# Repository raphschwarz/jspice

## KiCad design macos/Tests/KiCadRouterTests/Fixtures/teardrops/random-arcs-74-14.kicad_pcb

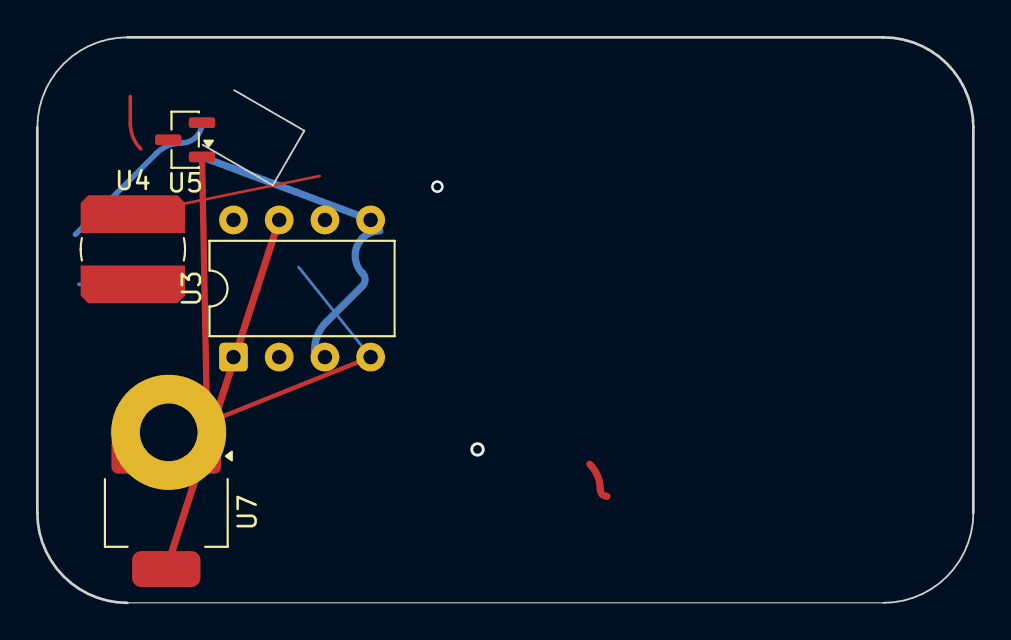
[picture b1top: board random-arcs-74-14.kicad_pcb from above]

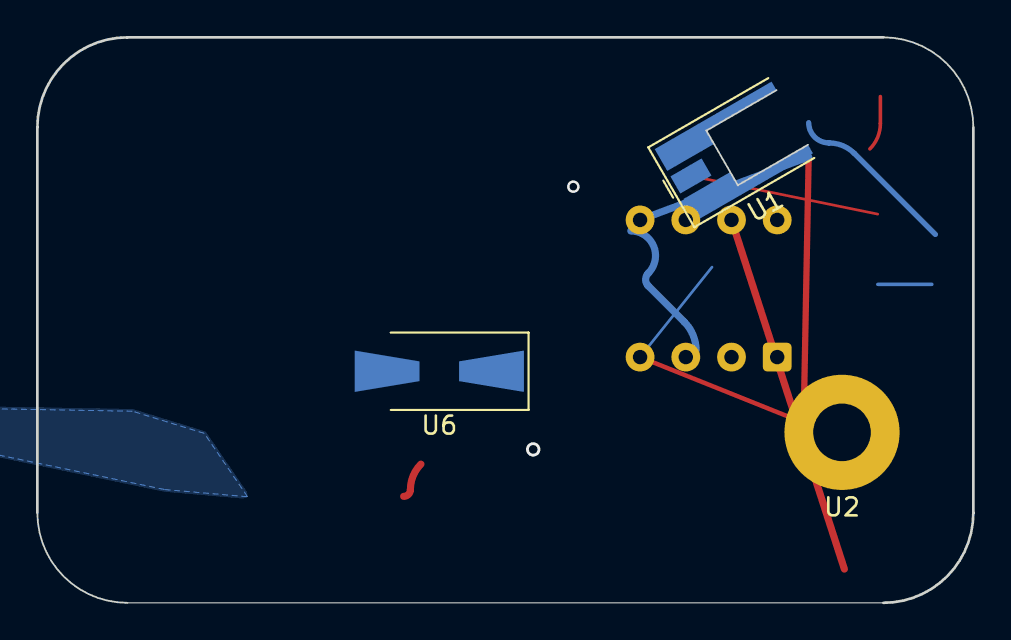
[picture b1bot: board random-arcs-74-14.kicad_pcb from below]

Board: 2 copper layers, 52.0 x 31.4 mm, 7 parts (3 on the bottom side), 6 nets.

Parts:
U1: MMCX_Molex_73415-0961_Horizontal_0.8mm-PCB
U2: MountingHole_3.2mm_M3_Pad
U3: DIP-8_W7.62mm
U4: L_Bourns_SDR0604
U5: SOT-23
U6: D_SMA-SMB_Universal_Handsoldering
U7: SOT-223-3_TabPin2

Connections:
/sub/clk: U3.3, U3.6
D7: U3.2, U6.2, U7.2
N2: U2.1, U3.4
SIG1: U1.1, U5.1, U5.3
SIG2: U6.1, U7.2, U7.3
VCC: U4.2, U5.2

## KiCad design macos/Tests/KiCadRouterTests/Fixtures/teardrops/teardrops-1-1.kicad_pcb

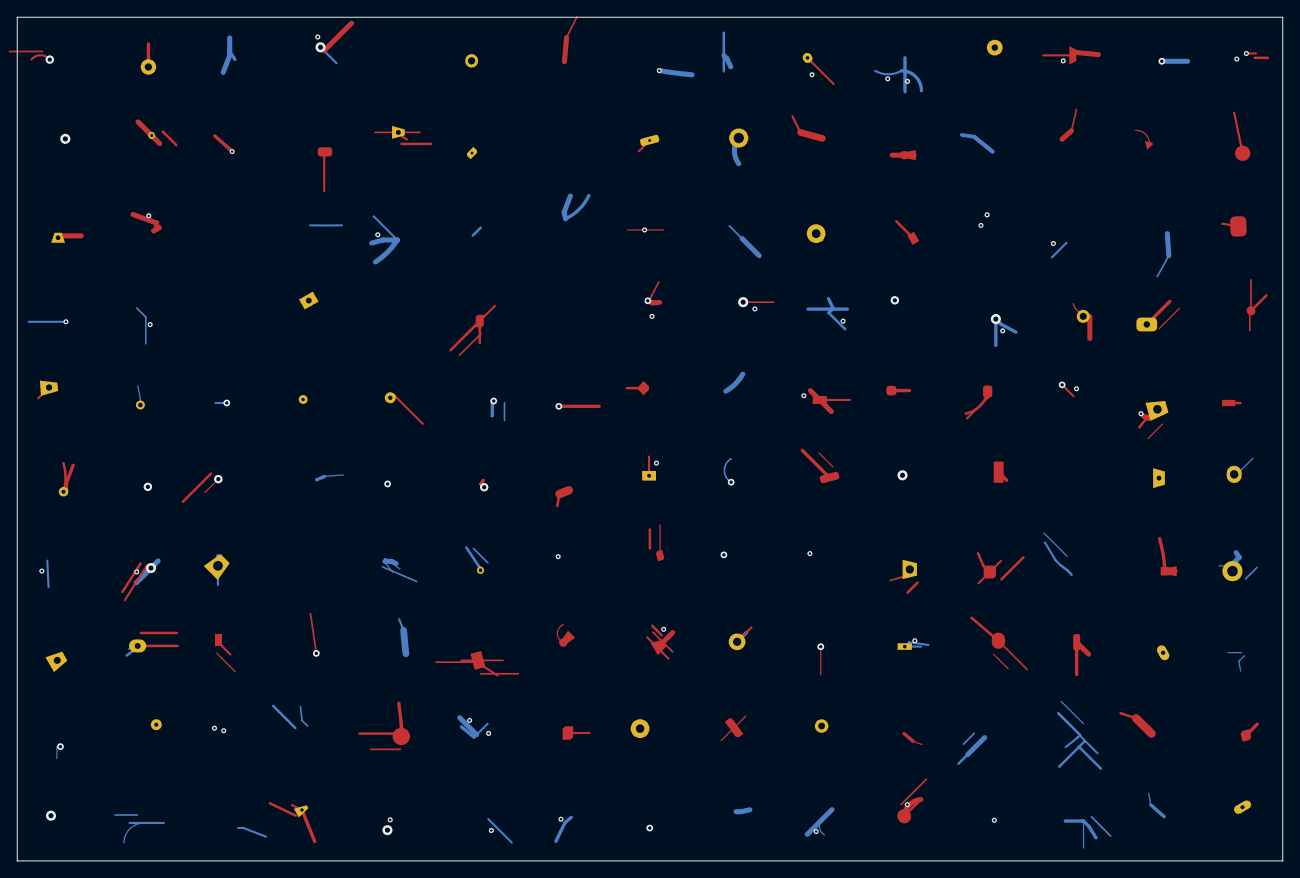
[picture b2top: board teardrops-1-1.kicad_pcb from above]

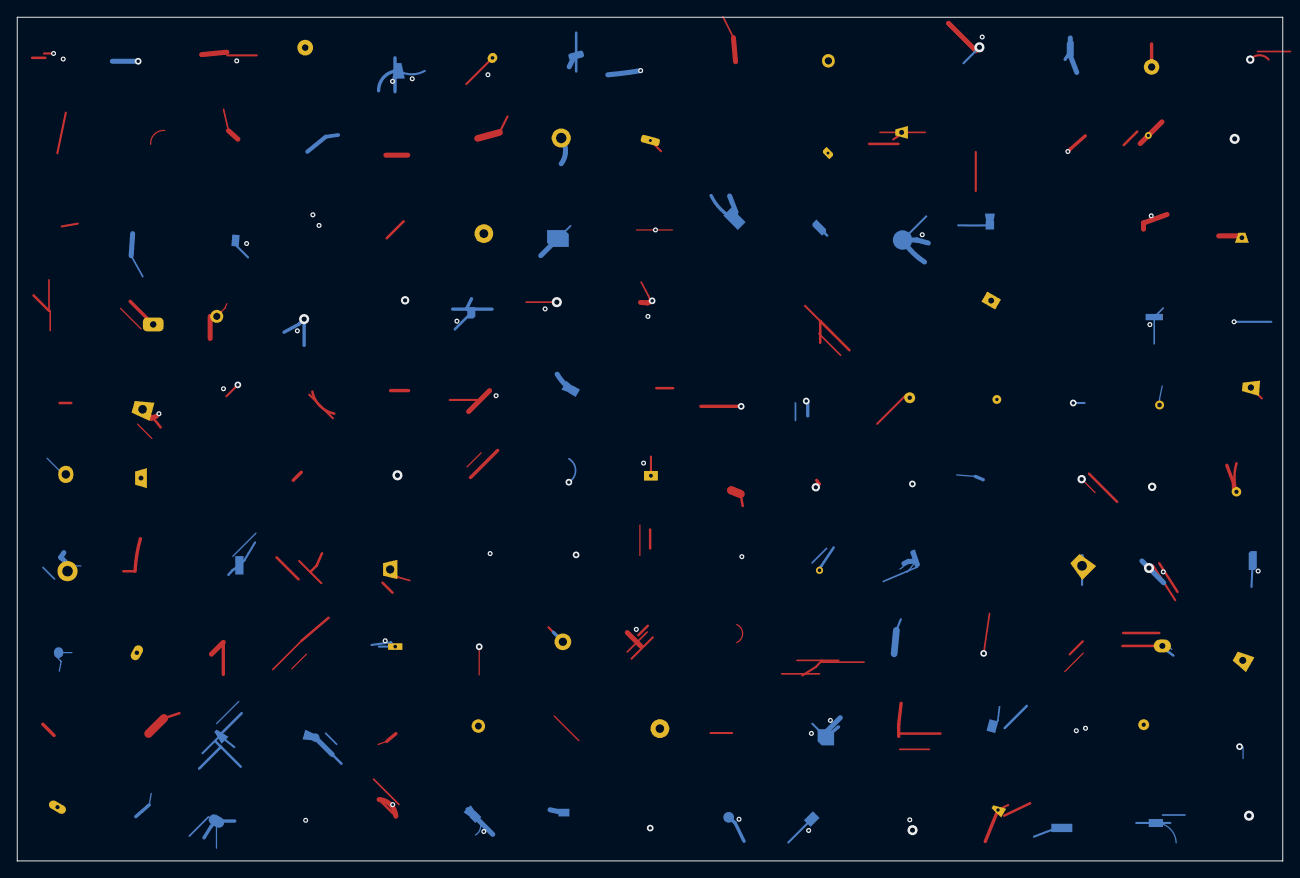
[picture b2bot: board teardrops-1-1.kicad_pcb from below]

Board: 4 copper layers, 150.0 x 100.0 mm, 95 parts (27 on the bottom side), 10 nets.

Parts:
U5_25, U5_45, U5_55, U5_65, U5_75, U15_5, U15_15, U15_25, U15_35, U15_45, U15_75, U15_85, U15_95, U25_5, U25_65, U25_75, U25_95, U35_15, U35_25, U35_35, U35_45, U35_85, U35_95, U45_15, U45_25, U45_45, U45_65, U45_85, U55_5, U55_15, U55_25, U55_35, U55_65, U55_75, U55_85, U55_95, U65_25, U65_75, U65_85, U65_95, U75_15, U75_45, U75_55, U75_65, U75_75, U75_85, U85_5, U85_15, U85_25, U85_45, U85_75, U85_85, U85_95, U95_5, U95_25, U95_35, U95_45, U95_55, U95_85, U95_95, U105_5, U105_15, U105_25, U105_45, U105_65, U105_75, U105_95, U115_5, U115_45, U115_55, U115_65, U115_75, U115_85, U125_5, U125_25, U125_35, U125_65, U125_75, U125_85, U125_95, U135_15, U135_35, U135_45, U135_55, U135_65, U135_75, U145_15, U145_25, U145_35, U145_45, U145_55, U145_65, U145_75, U145_85, U145_95: (no value)

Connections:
N0: U15_25.1, U55_95.1, U125_35.1, U135_55.1
N1: U5_45.1, U5_55.1, U25_95.1, U35_15.1, U45_15.1, U55_25.1, U95_25.1, U105_65.1, U115_45.1, U115_85.1, U125_5.1, U135_65.1
N2: U15_5.1, U25_5.1, U45_85.1, U55_35.1, U75_55.1, U85_85.1, U95_5.1, U115_55.1, U125_65.1
N3: U15_35.1, U25_75.1, U35_35.1, U35_45.1, U55_65.1, U65_95.1, U85_25.1, U85_75.1, U85_95.1, U95_95.1, U105_5.1, U125_75.1, U135_15.1, U145_15.1, U145_55.1
N4: U5_25.1, U35_95.1, U45_45.1, U55_15.1, U75_45.1, U85_5.1, U95_55.1, U105_15.1, U125_25.1, U135_45.1, U145_45.1, U145_65.1
N5: U45_65.1, U55_5.1, U75_65.1, U75_75.1, U75_85.1, U105_45.1, U105_95.1, U115_5.1, U125_85.1, U145_35.1
N6: U15_75.1, U45_25.1, U55_85.1, U85_45.1, U95_45.1, U95_85.1, U115_65.1, U145_95.1
N7: U5_65.1, U5_75.1, U65_25.1, U65_85.1, U85_15.1, U105_75.1, U115_75.1, U135_75.1, U145_25.1
N8: U15_45.1, U15_85.1, U15_95.1, U25_65.1, U55_75.1, U65_75.1, U135_35.1, U145_85.1
N9: U15_15.1, U35_25.1, U35_85.1, U75_15.1, U95_35.1, U105_25.1, U125_95.1, U145_75.1

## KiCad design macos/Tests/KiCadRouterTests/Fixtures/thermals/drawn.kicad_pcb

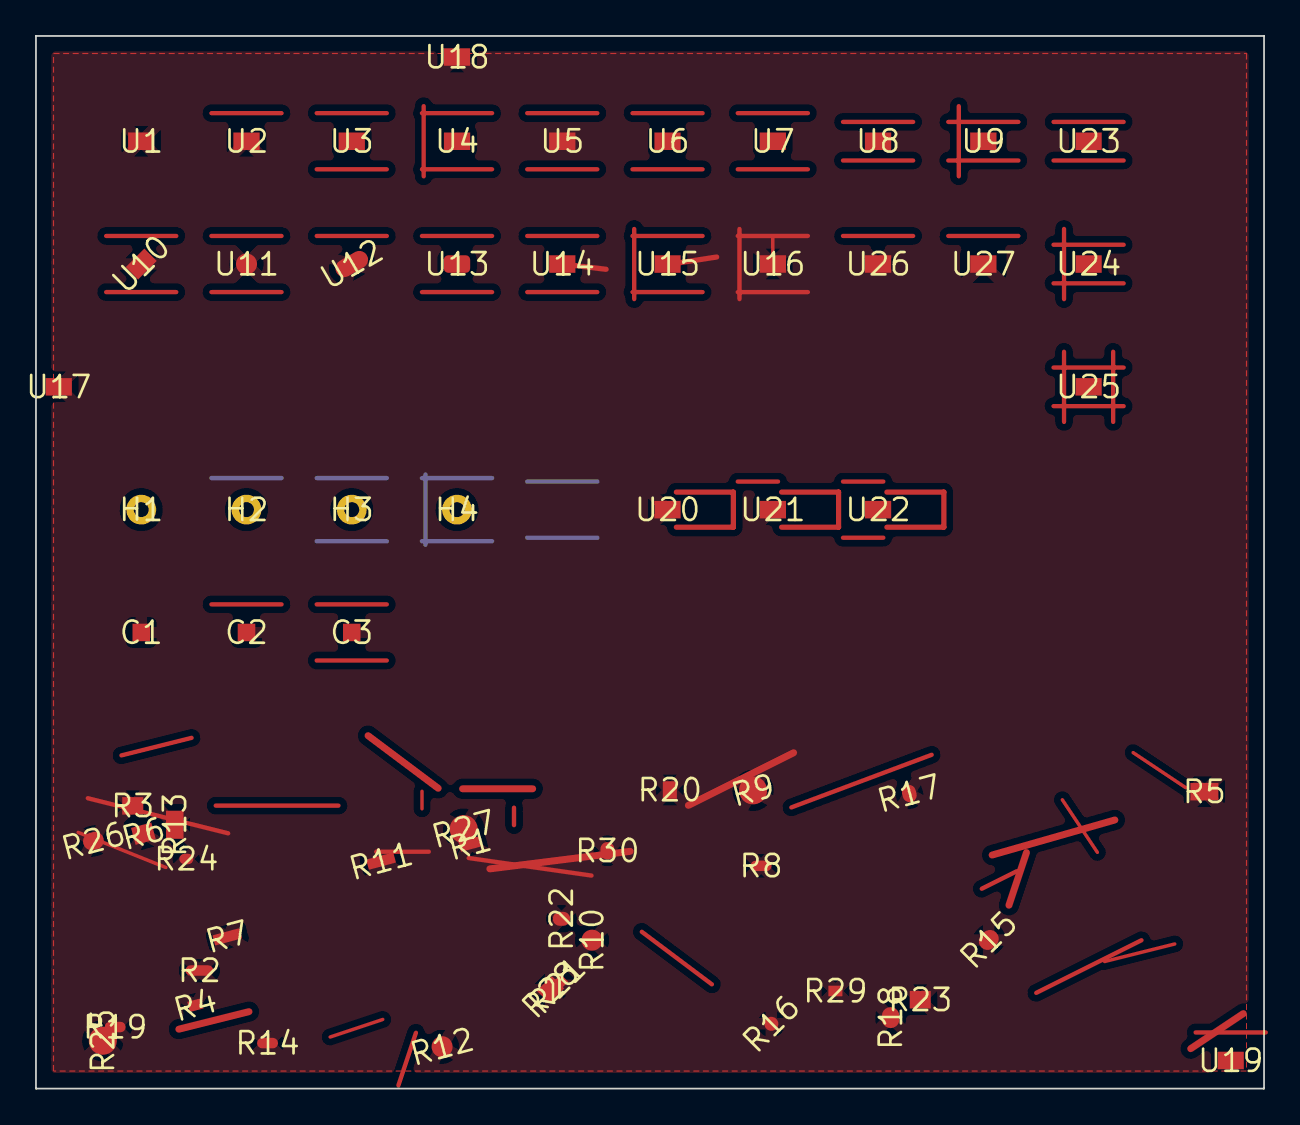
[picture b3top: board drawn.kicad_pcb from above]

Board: 2 copper layers, 70.0 x 60.0 mm, 65 parts (1 on the bottom side), 2 nets.

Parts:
C1, C2, C3: (no value)
H1, H2, H3, H4, H5: (no value)
R1, R2, R3, R4, R5, R6, R7, R8, R9, R10, R11, R12, R13, R14, R15, R16, R17, R18, R19, R20, R21, R22, R23, R24, R25, R26, R27, R28, R29, R30: (no value)
U1, U2, U3, U4, U5, U6, U7, U8, U9, U10, U11, U12, U13, U14, U15, U16, U17, U18, U19, U20, U21, U22, U23, U24, U25, U26, U27: (no value)

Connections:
GND: C1.1, C2.1, C3.1, R1.1, R2.1, R3.1, R4.1, R5.1, R6.1, R7.1, R8.1, R9.1, R10.1, R11.1, R12.1, R13.1, R14.1, R15.1, R16.1, R17.1, R18.1, R19.1, R20.1, R21.1, R22.1, R23.1, R24.1, R25.1, R26.1, R27.1, R28.1, R29.1, R30.1, U1.1, U2.1, U3.1, U4.1, U5.1, U6.1, U7.1, U8.1, U9.1, U10.1, U11.1, U12.1, U13.1, U14.1, U15.1, U16.1, U17.1, U18.1, U19.1, U20.1, U21.1, U22.1, U23.1, U24.1, U25.1, U26.1, U27.1
VCC: H1.1, H2.1, H3.1, H4.1, H5.1

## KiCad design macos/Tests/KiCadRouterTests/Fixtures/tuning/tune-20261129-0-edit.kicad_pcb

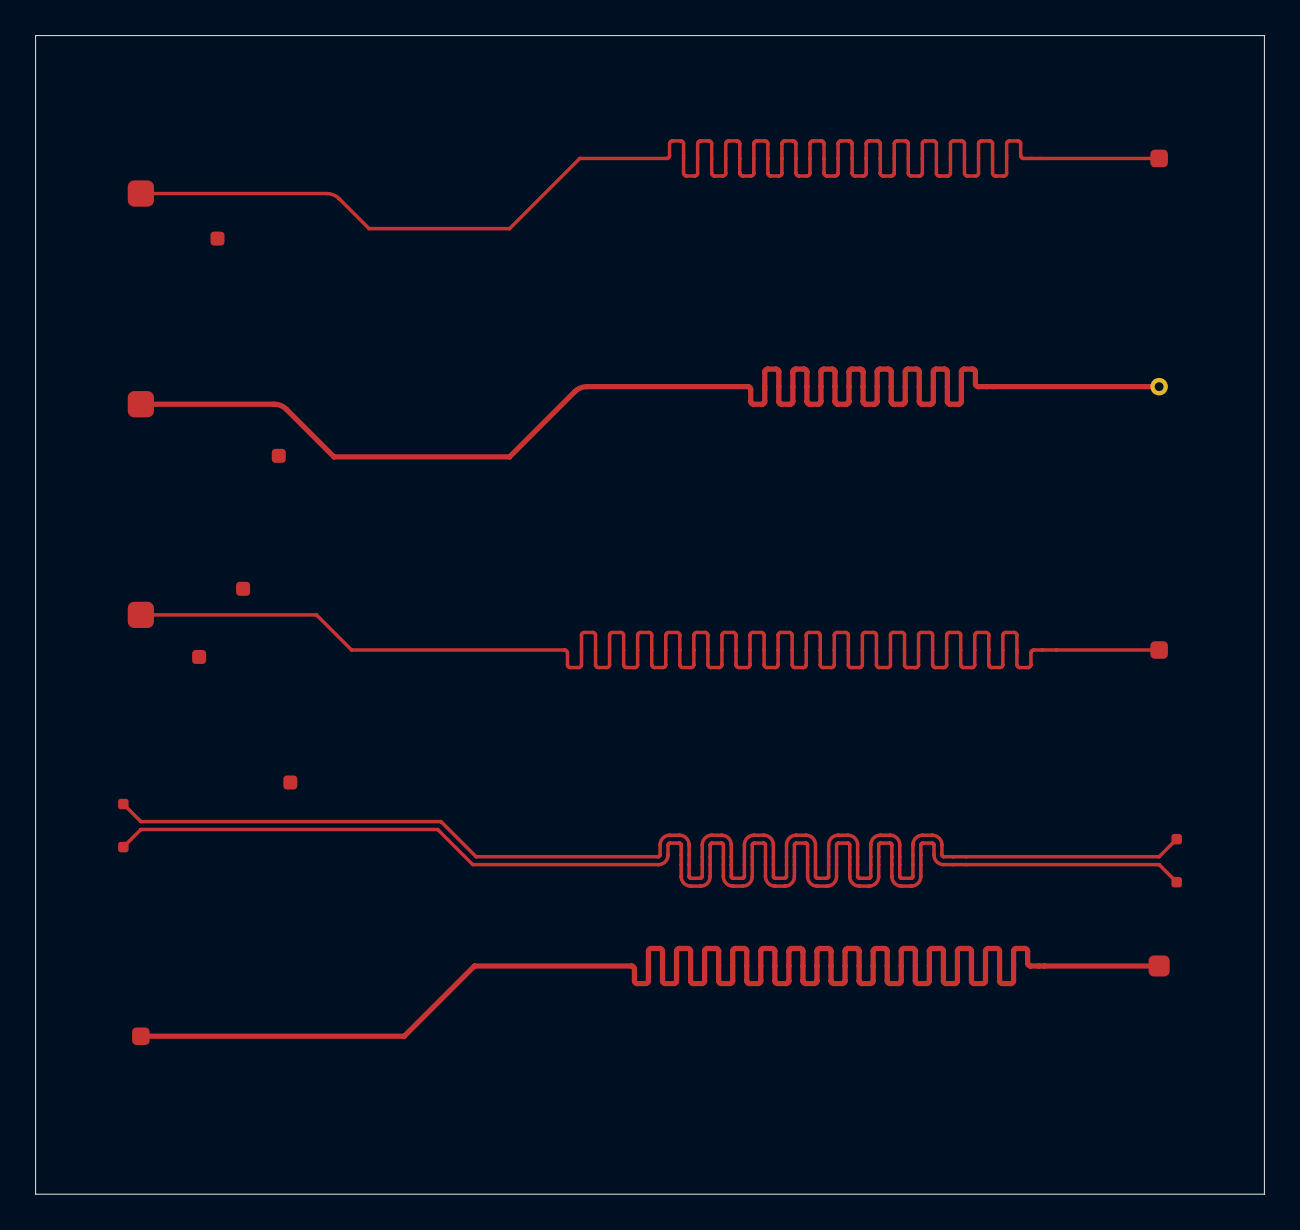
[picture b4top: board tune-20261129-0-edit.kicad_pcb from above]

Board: 2 copper layers, 70.0 x 66.0 mm, 17 parts (0 on the bottom side), 6 nets.

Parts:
P1, P5, P15, P19, P23, P34, P38, P42, P49, P53, P57, P61, P65, P69, P83, P87, P91: Pad

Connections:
D4_N: P65.1, P69.1
D4_P: P57.1, P61.1
S1: P1.1, P5.1
S2: P19.1, P23.1
S3: P38.1, P42.1
S5: P87.1, P91.1
